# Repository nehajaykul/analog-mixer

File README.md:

# 2-Channel-Analog-DJ-Mixer

A fully analog 2-channel DJ mixer designed from first principles, 
simulated in LTspice, and laid out in KiCad for JLCPCB fabrication.

## Signal Chain

[3.5mm Input] → [L+R Sum] → [Sallen-Key HPF] → [SVF EQ Stage 1: 200Hz]
    → [SVF EQ Stage 2: 4kHz] → [Gain/Trim] → [Channel Fader]
    → [Crossfader] → [Virtual-Earth Sum] → [Master Output]

## Features

- 3-band parametric EQ per channel (HI/MID/LOW) with kill switches
- Cascaded Kerwin-Huelsman-Newcomb state-variable filters; Qs chosen for maximum passband flatness
  - Stage 1: f₀ = 200 Hz, Q = ~1.0
  - Stage 2: f₀ = 4 kHz, Q = ~.83
- Reduced summing-node phase cancellation, achieving <1.1 dB response variation across the band-pass (200 Hz–4 kHz)
- Pre-fader listen (PFL) cue system with headphone output; tapped after gain/trim stage and before channel fader
- Clipping LED indicator with 9.1V zener threshold (~11V signal threshold)
- Isolated ±15V dual-rail power supply (Traco TMR 6-1223)
- 15+ NE5532/TL072 op-amps throughout signal path

## Specifications

| Parameter | Value |
|-----------|-------|
| Input | 3.5mm TRS, line level |
| EQ crossovers | 200 Hz, 4 kHz |
| EQ range | Cut to +14 dB per band |
| Power supply | 12V DC input → ±15V isolated |
| Op-amps | NE5532 (signal path), TL072 (monitor path) |
| PCB | 2-layer, JLCPCB fabrication |

## Repository Structure

```
/ltspice     — LTspice simulation files (.asc) for each circuit stage
/kicad       — KiCad schematic (.kicad_sch) and PCB layout (.kicad_pcb)
/gerbers     — Fabrication files for JLCPCB 2-layer PCB production
/docs        — Schematic PDF, simulation result plots, BOM
README.md    — Project overview
```

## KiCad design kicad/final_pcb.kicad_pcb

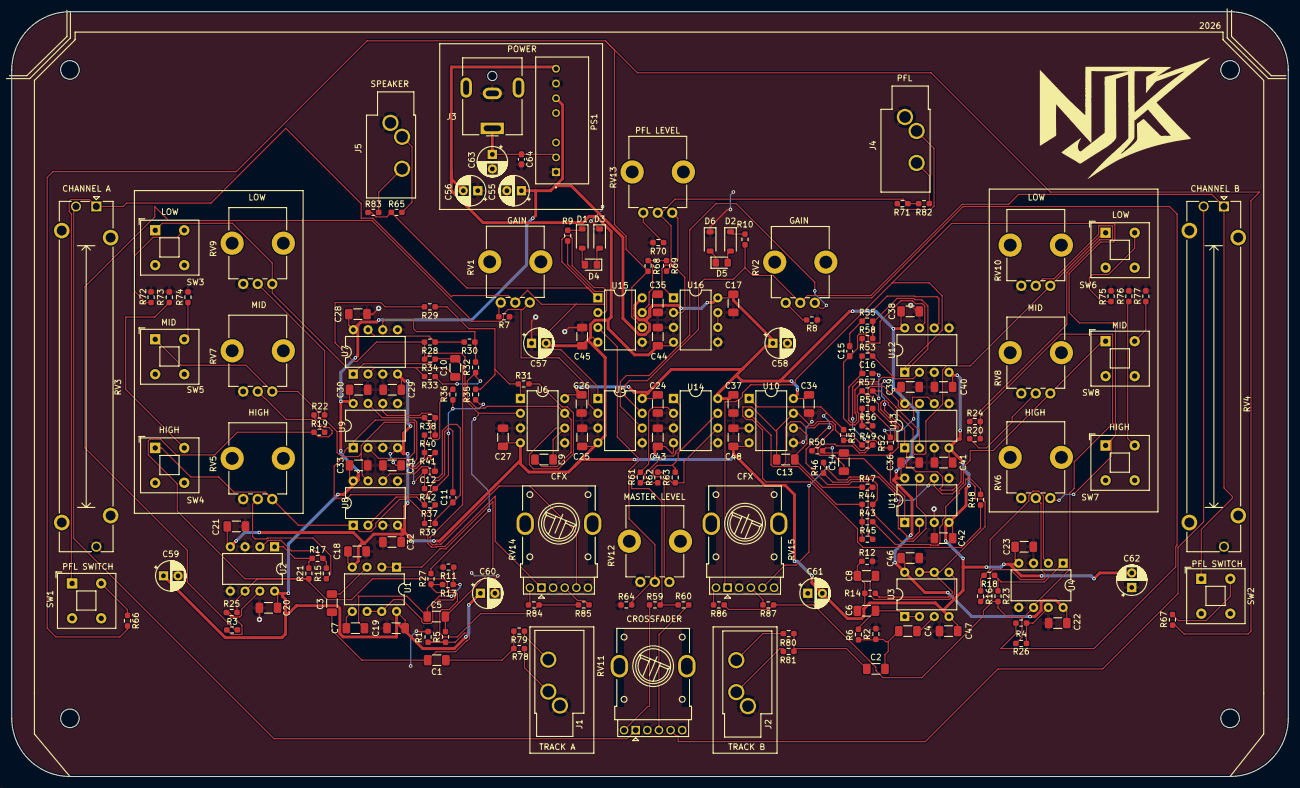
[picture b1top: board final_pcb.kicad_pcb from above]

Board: 2 copper layers, 219.5 x 131.5 mm, 196 parts (0 on the bottom side), 112 nets.

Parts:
C1, C2, C3, C4, C5, C6, C7, C8, C9, C10, C13, C14, C17, C18, C19, C20, C21, C22, C23, C24, C25, C26, C27, C28, C29, C30, C31, C32, C33, C34, C35, C36, C37, C38, C39, C40, C41, C42, C43, C44, C45, C46, C47, C48: 100n; C_1206_3216Metric_Pad1.33x1.80mm_HandSolder
C11, C12, C15, C16: 10n; C_0603_1608Metric_Pad1.08x0.95mm_HandSolder
C55, C56, C57, C58, C59, C60, C61, C62, C63: 22u; CP_Radial_D5.0mm_P2.50mm
C64: 100n; C_0603_1608Metric_Pad1.08x0.95mm_HandSolder
D1, D2, D3, D6: 9.1; D_SOD-123
D4, D5: D; LED_0805_2012Metric_Pad1.15x1.40mm_HandSolder
J1, J2, J4, J5: AudioJack3; Jack_3.5mm_CUI_SJ1-3533NG_Horizontal_CircularHoles
J3: Barrel_Jack; BarrelJack_CUI_PJ-063AH_Horizontal
PS1: TMR_6-1223; CONV_TMR_6-1223
R1, R2, R5, R6, R11, R12, R13, R14, R64: 100K; R_0603_1608Metric_Pad0.98x0.95mm_HandSolder
R3, R4, R19, R20, R21, R22, R23, R24, R25, R26, R27, R28, R29, R30, R34, R35, R36, R37, R38, R42, R43, R44, R45, R46, R50, R51, R52, R53, R54, R58, R59, R60, R61, R63, R66, R67, R69, R78, R79, R80, R81, R84, R85, R86, R87: 10K; R_0603_1608Metric_Pad0.98x0.95mm_HandSolder
R7, R8, R70: 500; R_0603_1608Metric_Pad0.98x0.95mm_HandSolder
R9, R10: 390; R_0603_1608Metric_Pad0.98x0.95mm_HandSolder
R15, R16, R17, R18, R62: 3.3K; R_0603_1608Metric_Pad0.98x0.95mm_HandSolder
R31, R33, R47, R49: 8.2K; R_0603_1608Metric_Pad0.98x0.95mm_HandSolder
R32, R48: 5K; R_0603_1608Metric_Pad0.98x0.95mm_HandSolder
R39, R41, R55, R57: 3.9K; R_0603_1608Metric_Pad0.98x0.95mm_HandSolder
R40, R56: 6K; R_0603_1608Metric_Pad0.98x0.95mm_HandSolder
R65, R83: 47; R_0603_1608Metric_Pad0.98x0.95mm_HandSolder
R68: 7.8K; R_0603_1608Metric_Pad0.98x0.95mm_HandSolder
R71, R82: 150; R_0603_1608Metric_Pad0.98x0.95mm_HandSolder
R72, R73, R74, R75, R76, R77: 100; R_0603_1608Metric_Pad0.98x0.95mm_HandSolder
RV1, RV2, RV5, RV6, RV7, RV8, RV9, RV10, RV12, RV13: 50K; Potentiometer_Bourns_PTV09A-1_Single_Vertical
RV3, RV4: 10K; Potentiometer_Bourns_PTA4543_Single_Slide
RV11, RV14, RV15: 10K; Potentiometer_Bourns_PTV112-4_Dual_Vertical
SW1, SW2, SW3, SW4, SW5, SW6, SW7, SW8: SW_SPST; SW_Push_2P1T_Toggle_CK_PVA1xxH1xxxxxxV2
U1, U2, U3, U4, U5, U6, U7, U8, U9, U10, U11, U12, U13, U14: NE5532; DIP-8_W7.62mm
U15, U16: TL072; DIP-8_W7.62mm

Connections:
+15V: C17.1, C19.1, C20.1, C22.1, C24.1, C26.1, C28.1, C30.1, C33.1, C34.1, C35.1, C36.1, C37.1, C38.1, C39.1, C46.1, C55.1, C58.1, C59.1, C60.1, PS1.6 (+VOUT), U1.8 (V+), U2.8 (V+), U3.8 (V+), U4.8 (V+), U5.8 (V+), U6.8 (V+), U7.8 (V+), U8.8 (V+), U9.8 (V+), U10.8 (V+), U11.8 (V+), U12.8 (V+), U13.8 (V+), U14.8 (V+), U15.8 (V+), U16.8 (V+)
-15V: C18.2, C21.2, C23.2, C25.2, C27.2, C29.2, C31.2, C32.2, C40.2, C41.2, C42.2, C43.2, C44.2, C45.2, C47.2, C48.2, C56.2, C57.2, C61.2, C62.2, PS1.8 (-VOUT), U1.4 (V-), U2.4 (V-), U3.4 (V-), U4.4 (V-), U5.4 (V-), U6.4 (V-), U7.4 (V-), U8.4 (V-), U9.4 (V-), U10.4 (V-), U11.4 (V-), U12.4 (V-), U13.4 (V-), U14.4 (V-), U15.4 (V-), U16.4 (V-)
/a_svf/a_svf_in: R13.2, R27.1, U1.6 (-), U1.7
/a_svf/band_pass_a: C12.2, R42.2, RV7.1, SW5.1 (A), U9.1
/a_svf/high_pass_a: R37.2, R39.1, RV5.1, RV14.1, SW4.1 (A), U8.1
/a_svf/low_pass_a: C10.2, R34.2, RV9.1, RV14.6, SW3.1 (A), U7.1
/b_svf/b_svf_in: R14.2, R43.1, U3.6 (-), U3.7
/b_svf/band_pass_b: C16.2, R58.2, RV8.1, SW8.1 (A), U13.1
/b_svf/high_pass_b: R53.2, R55.1, RV6.1, RV15.1, SW7.1 (A), U12.1
/b_svf/low_pass_b: C14.2, R50.2, RV10.1, RV15.6, SW6.1 (A), U11.1
/gain_in_a: R3.1, R25.2, U2.7
/gain_in_b: R4.1, R26.2, U4.7
/pfl_a: R9.1, RV1.2, RV3.1, SW1.1 (A), U5.1
/pfl_b: R10.1, RV2.2, RV4.1, SW2.1 (A), U5.7
/summing/a_out: RV3.2, RV11.1
/summing/b_out: RV4.2, RV11.6
GND: C17.2, C18.1, C19.2, C20.2, C21.1, C22.2, C23.1, C24.2, C25.1, C26.2, C27.1, C28.2, C29.1, C30.2, C31.1, C32.1, C33.2, C34.2, C35.2, C36.2, C37.2, C38.2, C39.2, C40.1, C41.1, C42.1, C43.1, C44.1, C45.1, C46.2, C47.1, C48.1, C55.2, C56.1, C57.1, C58.2, C59.2, C60.2, C61.1, C62.1, C63.2, C64.2, D3.1 (K), D6.1 (K), J1.S, J2.S, J3.2, J4.S, J5.S, PS1.1 (-VIN(GND)), PS1.7 (COMMON), R1.2, R2.2, R7.1, R8.1, R11.2, R12.2, R64.1, R70.1, R72.2, R73.2, R74.2, R75.2, R76.2, R77.2, RV3.3, RV4.3, RV5.3, RV6.3, RV7.3, RV8.3, RV9.3, RV10.3, RV11.3, RV11.4, RV12.3, RV14.3, RV14.4, RV15.3, RV15.4, U2.3 (+), U2.5 (+), U4.3 (+), U4.5 (+), U5.3 (+), U5.5 (+), U6.3 (+), U6.5 (+), U7.3 (+), U7.5 (+), U8.3 (+), U8.5 (+), U9.3 (+), U9.5 (+), U10.3 (+), U10.5 (+), U11.3 (+), U11.5 (+), U12.3 (+), U12.5 (+), U13.3 (+), U13.5 (+), U14.3 (+), U14.5 (+), U15.5 (+), U16.3 (+), U16.5 (+)
unnamed: C1.1, R78.2, R79.2
unnamed: C1.2, C3.1, R1.1, R5.1
unnamed: C2.1, R80.2, R81.2
unnamed: C2.2, C4.1, R2.1, R6.1
unnamed: C5.2, C7.1, R11.1, R13.1
unnamed: C6.2, C8.1, R12.1, R14.1
unnamed: C9.2, R32.2, R33.1, U6.7
unnamed: C11.2, R40.2, R41.1, U8.7
unnamed: C13.2, R48.2, R49.1, U10.7
unnamed: C15.2, R56.2, R57.1, U12.7
unnamed: D1.2 (A), D4.2 (A)
unnamed: D1.1 (K), R9.2
unnamed: D2.2 (A), D5.2 (A)
unnamed: D2.1 (K), R10.2
unnamed: D3.2 (A), D4.1 (K)
unnamed: D5.1 (K), D6.2 (A)
unnamed: J1.R, R79.1
unnamed: J1.T, R78.1
unnamed: J2.R, R80.1
unnamed: J2.T, R81.1
unnamed: J4.R, R82.2
unnamed: J4.T, R71.2
unnamed: J5.R, R83.2
unnamed: J5.T, R65.2
unnamed: C63.1, C64.1, J3.1, PS1.2 (+VIN(VCC))
unnamed: R7.2, RV1.3
unnamed: R8.2, RV2.3
unnamed: R15.1, RV5.2
unnamed: R16.1, RV6.2
unnamed: R17.2, R21.1, U2.1
unnamed: R18.2, R23.1, U4.1
unnamed: R19.1, RV7.2
unnamed: R20.1, RV8.2
unnamed: R22.1, RV9.2
unnamed: R24.1, RV10.2
unnamed: R28.2, R30.1, U7.7
unnamed: R29.2, R31.1, R35.1, U6.1
unnamed: R36.2, R38.1, U9.7
unnamed: R44.2, R46.1, U11.7
unnamed: R45.2, R47.1, R51.1, U10.1
unnamed: R52.2, R54.1, U13.7
unnamed: R59.1, RV11.2
unnamed: R60.1, RV11.5
unnamed: R61.2, R62.1, U14.1
unnamed: R63.2, RV12.1, U14.7
unnamed: R68.2, R69.1, U15.7
unnamed: R70.2, RV13.3
unnamed: R71.1, R82.1, RV13.2, U16.1
unnamed: R84.1, RV14.2
unnamed: R85.1, RV14.5
unnamed: R86.1, RV15.2
unnamed: R87.1, RV15.5
unnamed: R66.1, SW1.2 (B)
unnamed: R67.1, SW2.2 (B)
unnamed: R72.1, SW3.2 (B)
unnamed: R73.1, SW4.2 (B)
unnamed: R74.1, SW5.2 (B)
unnamed: R75.1, SW6.2 (B)
unnamed: R76.1, SW7.2 (B)
unnamed: R77.1, SW8.2 (B)
unnamed: C3.2, U1.3 (+)
unnamed: C5.1, R5.2, U1.1, U1.2 (-)
unnamed: C7.2, U1.5 (+)
unnamed: R15.2, R17.1, U2.2 (-)
unnamed: R19.2, R21.2, R22.2, R25.1, R84.2, R85.2, U2.6 (-)
unnamed: C4.2, U3.3 (+)
unnamed: C6.1, R6.2, U3.1, U3.2 (-)
unnamed: C8.2, U3.5 (+)
unnamed: R16.2, R18.1, U4.2 (-)
unnamed: R20.2, R23.2, R24.2, R26.1, R86.2, R87.2, U4.6 (-)
unnamed: R3.2, RV1.1, U5.2 (-)
unnamed: R4.2, RV2.1, U5.6 (-)
unnamed: R27.2, R28.1, R29.1, R34.1, U6.2 (-)
unnamed: C9.1, R31.2, U6.6 (-)
unnamed: C10.1, R33.2, U7.2 (-)
unnamed: R30.2, R32.1, U7.6 (-)
unnamed: R35.2, R36.1, R37.1, R42.1, U8.2 (-)
unnamed: C11.1, R39.2, U8.6 (-)
unnamed: C12.1, R41.2, U9.2 (-)
unnamed: R38.2, R40.1, U9.6 (-)
unnamed: R43.2, R44.1, R45.1, R50.1, U10.2 (-)
unnamed: C13.1, R47.2, U10.6 (-)
unnamed: C14.1, R49.2, U11.2 (-)
unnamed: R46.2, R48.1, U11.6 (-)
unnamed: R51.2, R52.1, R53.1, R58.1, U12.2 (-)
unnamed: C15.1, R55.2, U12.6 (-)
unnamed: C16.1, R57.2, U13.2 (-)
unnamed: R54.2, R56.1, U13.6 (-)
unnamed: R59.2, R60.2, R61.1, U14.2 (-)
unnamed: R62.2, R63.1, U14.6 (-)
unnamed: R64.2, RV12.2, U15.3 (+)
unnamed: R65.1, R83.1, U15.1, U15.2 (-)
unnamed: R66.2, R67.2, R68.1, U15.6 (-)
unnamed: R69.2, RV13.1, U16.2 (-)
unnamed: U16.6 (-), U16.7

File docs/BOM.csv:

"Id";"Designator";"Footprint";"Quantity";"Designation";"Supplier and ref";
1;"C19,C29,C28,C25,C14,C9,C45,C18,C42,C4,C41,C8,C32,C36,C47,C23,C1,C6,C44,C35,C46,C30,C26,C2,C43,C31,C22,C17,C33,C48,C20,C10,C40,C27,C37,C7,C34,C5,C38,C21,C3,C13,C39,C24";"C_1206_3216Metric_Pad1.33x1.80mm_HandSolder";44;"100n";;;
2;"R29,R85,R59,R60,R24,R46,R21,R81,R58,R50,R69,R63,R87,R80,R54,R4,R20,R36,R19,R43,R44,R67,R30,R35,R22,R79,R84,R53,R27,R78,R66,R52,R42,R23,R37,R38,R86,R28,R61,R3,R25,R34,R51,R26,R45";"R_0603_1608Metric_Pad0.98x0.95mm_HandSolder";45;"10K";;;
3;"SW4,SW6,SW7,SW5,SW3,SW2,SW1,SW8";"SW_Push_2P1T_Toggle_CK_PVA1xxH1xxxxxxV2";8;"SW_SPST";;;
4;"RV11,RV15,RV14";"Potentiometer_Bourns_PTV112-4_Dual_Vertical";3;"10K";;;
5;"R18,R62,R17,R15,R16";"R_0603_1608Metric_Pad0.98x0.95mm_HandSolder";5;"3.3K";;;
6;"J5,J2,J1,J4";"Jack_3.5mm_CUI_SJ1-3533NG_Horizontal_CircularHoles";4;"AudioJack3";;;
7;"R65,R83";"R_0603_1608Metric_Pad0.98x0.95mm_HandSolder";2;"47";;;
8;"RV7,RV12,RV9,RV2,RV13,RV10,RV8,RV1,RV6,RV5";"Potentiometer_Bourns_PTV09A-1_Single_Vertical";10;"50K";;;
9;"U1,U8,U3,U6,U5,U11,U7,U4,U12,U10,U13,U2,U14,U9";"DIP-8_W7.62mm";14;"NE5532";;;
10;"R74,R75,R73,R77,R72,R76";"R_0603_1608Metric_Pad0.98x0.95mm_HandSolder";6;"100";;;
11;"R11,R1,R12,R5,R2,R64,R14,R13,R6";"R_0603_1608Metric_Pad0.98x0.95mm_HandSolder";9;"100K";;;
12;"R48,R32";"R_0603_1608Metric_Pad0.98x0.95mm_HandSolder";2;"5K";;;
13;"R47,R49,R33,R31";"R_0603_1608Metric_Pad0.98x0.95mm_HandSolder";4;"8.2K";;;
14;"D4,D5";"LED_0805_2012Metric_Pad1.15x1.40mm_HandSolder";2;"D";;;
15;"C55,C56,C58,C62,C60,C59,C63,C57,C61";"CP_Radial_D5.0mm_P2.50mm";9;"22u";;;
16;"D6,D3,D2,D1";"D_SOD-123";4;"9.1";;;
17;"R9,R10";"R_0603_1608Metric_Pad0.98x0.95mm_HandSolder";2;"390";;;
18;"R40,R56";"R_0603_1608Metric_Pad0.98x0.95mm_HandSolder";2;"6K";;;
19;"C15,C11,C16,C12";"C_0603_1608Metric_Pad1.08x0.95mm_HandSolder";4;"10n";;;
20;"R71,R82";"R_0603_1608Metric_Pad0.98x0.95mm_HandSolder";2;"150";;;
21;"RV4,RV3";"Potentiometer_Bourns_PTA4543_Single_Slide";2;"10K";;;
22;"R68";"R_0603_1608Metric_Pad0.98x0.95mm_HandSolder";1;"7.8K";;;
23;"U16,U15";"DIP-8_W7.62mm";2;"TL072";;;
24;"R8,R70,R7";"R_0603_1608Metric_Pad0.98x0.95mm_HandSolder";3;"500";;;
25;"R57,R55,R39,R41";"R_0603_1608Metric_Pad0.98x0.95mm_HandSolder";4;"3.9K";;;
26;"C64";"C_0603_1608Metric_Pad1.08x0.95mm_HandSolder";1;"100n";;;
27;"J3";"BarrelJack_CUI_PJ-063AH_Horizontal";1;"Barrel_Jack";;;
28;"PS1";"CONV_TMR_6-1223";1;"TMR_6-1223";;;
